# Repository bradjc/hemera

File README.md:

Hemera Indoor Sensor Node
=========================

Hemera is an indoor wireless sensor node that measures temperature, humidity, light and motion.

The node contains three key sensors:
- Sensirion SHT11 (Temperature and Humidity)
- Rohm BH1721 (Light)
- PIR (Motion)

[

](http://www.bradcampbell.com/wp-content/uploads/2012/05/hemera_project.jpg)

Setup
-----

### 1) Clone &amp; install the Lab11 version of tinyos-main:

    git clone https://github.com/lab11/tinyos-main.git
    cd tinyos-main/tools
    ./Bootstrap
    ./configure
    make
    sudo make install

### 2) Clone yours truly:

    git clone https://github.com/lab11/hemera.git

### 3) Add to `bash.rc`:

    export TINYOS_ROOT_DIR=<path to>/tinyos-main
    export TINYOS_ROOT_DIR_ADDITIONAL=<path to>/hemera/tinyos:$TINYOS_ROOT_DIR_ADDITIONAL

### 4) Set up the RaspberryPi (optional, but recommended):

A modified RaspberryPi can be utilized to receive and forward data to GATD. 
If you choose to use one, you need the [Linux CC2520 Driver](https://github.com/ab500/linux-cc2520-driver) for the RPi.
Instead of installing this manually, it is suggested to download &amp; install the preinstalled image from [this torrent](https://github.com/lab11/raspberrypi-cc2520/tree/master/torrents).
Go to https://github.com/lab11/raspberrypi-cc2520 for additional details on setup.

Clone the RPi repo:

    git clone https://github.com/lab11/raspberrypi-cc2520.git

Add to `bash.rc`:

    export TINYOS_ROOT_DIR_ADDITIONAL=<path to>/raspberrypi-cc2520/tinyos:$TINYOS_ROOT_DIR_ADDITIONAL

### 5) Get the compilers

In order to compile the TinyOS code you need the msp430 and the ARM compilers

Sense Stuff
-----------

After you have finsihed the above setup, you should be ready to install apps on the Hemera board.

The basic sense &amp; broadcast app is HemeraAM. To install it, go to `<path to>/hemera/tinyos/apps/HemeraAM` and follow the README. 

To receive &amp; forward data to GATD on the RPi, go to `<path to>/hemera/tinyos/apps/RpiGatdForwarder` and follow the README.

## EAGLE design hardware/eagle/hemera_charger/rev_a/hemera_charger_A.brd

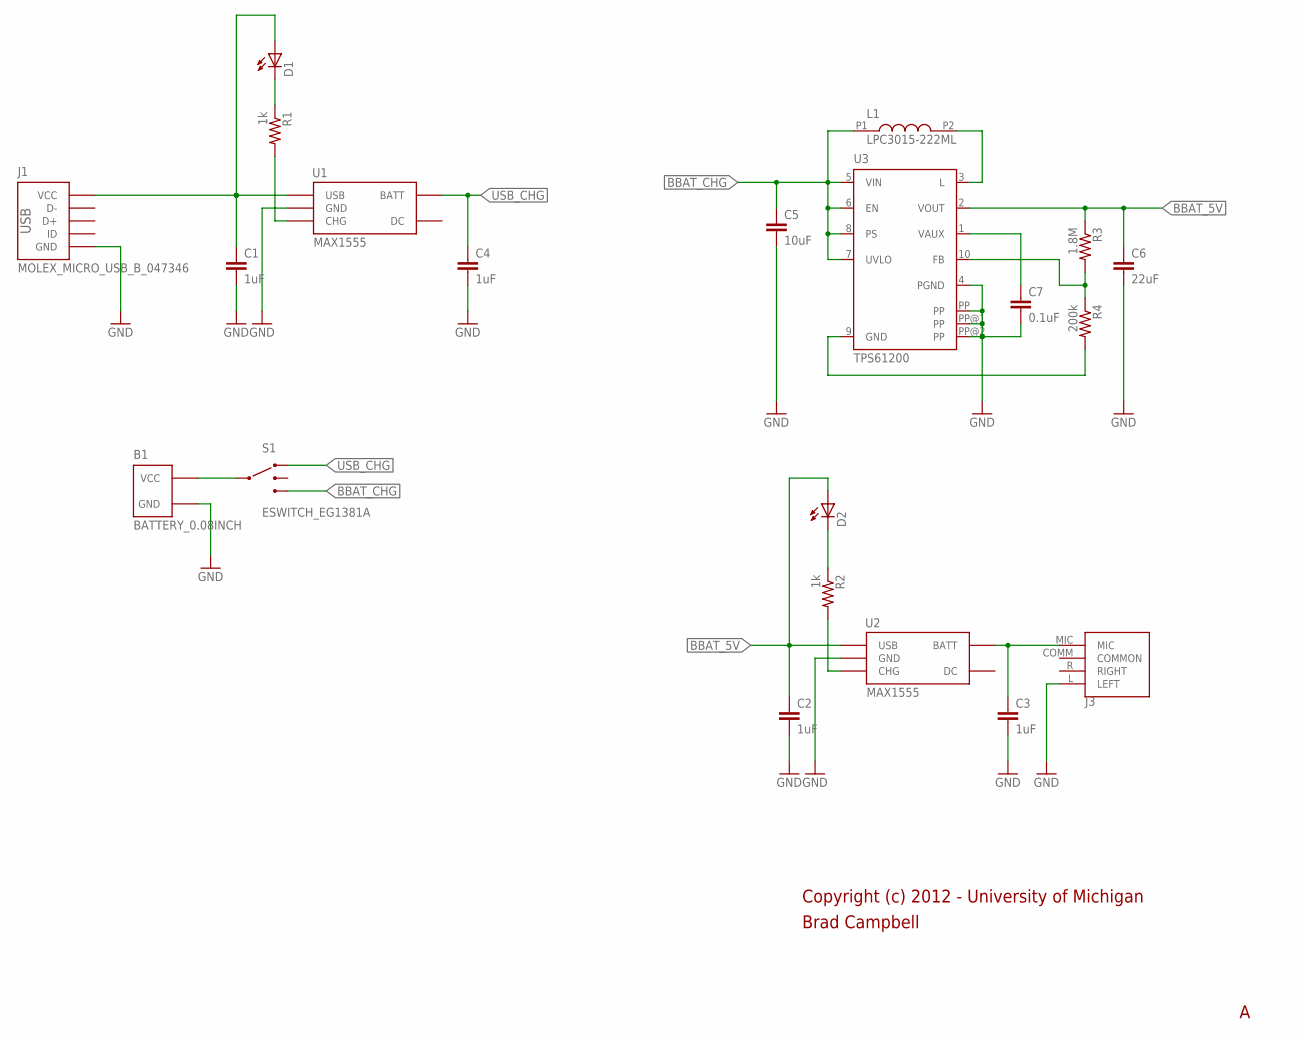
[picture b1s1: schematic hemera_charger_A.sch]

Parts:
B1: BATTERY_0.08INCH
C1, C2, C3, C4: 1uF; C0603
C5: 10uF; C0603
C6: 22uF; C0603
C7: 0.1uF; C0603
D1, D2: LED0603; LED-0603
J1: MOLEX_MICRO_USB_B_047346
J3: 3.5JACK4CONNSUNSTONE_QUICKTURN; PLUGBOARDCONNECTOR_SUNSTONE
L1: LPC3015-222ML; LPS3015
R1, R2: 1k; R0603
R3: 1.8M; R0603
R4: 200k; R0603
S1: ESWITCH_EG1381A; ESWITCH_EG1381
U1, U2: MAX1555; SOT23-5
U3: TPS61200; S-PDSO-N10

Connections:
BBAT: B1.POS (VCC), S1.3
BBAT_5V: C2.1, C6.1, D2.A, R3.1, U2.1 (USB), U3.2 (VOUT)
BBAT_CHG: C5.1, L1.P1 (1), S1.4, U3.5 (VIN), U3.6 (EN), U3.7 (UVLO), U3.8 (PS)
COMMON: J3.COMM (COMMON)
FB: R3.2, R4.1, U3.10 (FB)
GND: B1.NEG (GND), C1.2, C2.2, C3.2, C4.2, C5.2, C6.2, C7.2, J1.GND, J3.L (LEFT), U1.2 (GND), U2.2 (GND), U3.4 (PGND), U3.PP, U3.PP@1 (PP), U3.PP@2 (PP)
L: L1.P2 (2), U3.3 (L)
unnamed: C1.1, D1.A, J1.VCC, U1.1 (USB)
unnamed: R2.2, U2.3 (CHG)
unnamed: C3.1, J3.MIC, U2.5 (BATT)
unnamed: R1.2, U1.3 (CHG)
unnamed: D1.C, R1.1
unnamed: R4.2, U3.9 (GND)
unnamed: D2.C, R2.1
USB_CHG: C4.1, S1.1, U1.5 (BATT)
VAUX: C7.1, U3.1 (VAUX)

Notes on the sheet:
Brad Campbell
Copyright (c) 2012 - University of Michigan

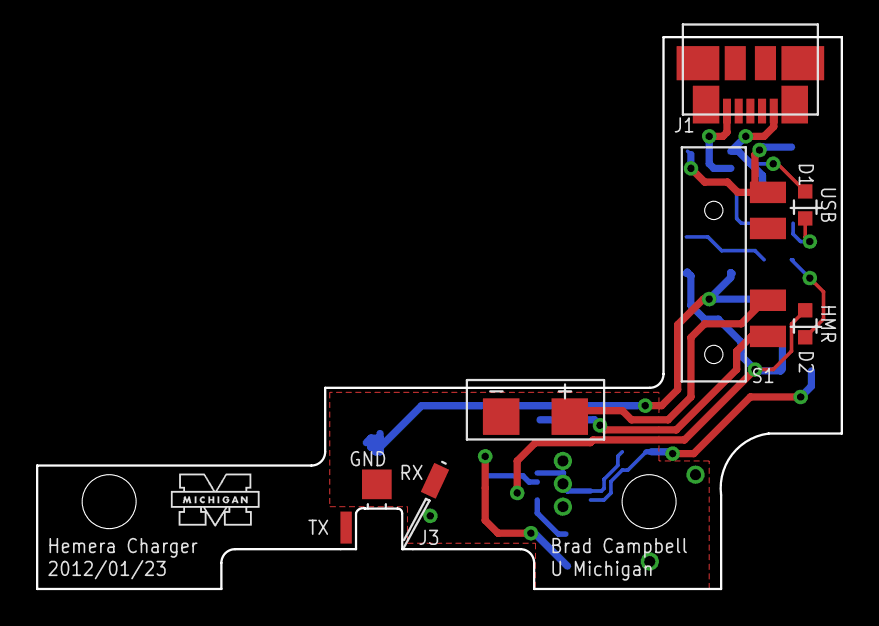
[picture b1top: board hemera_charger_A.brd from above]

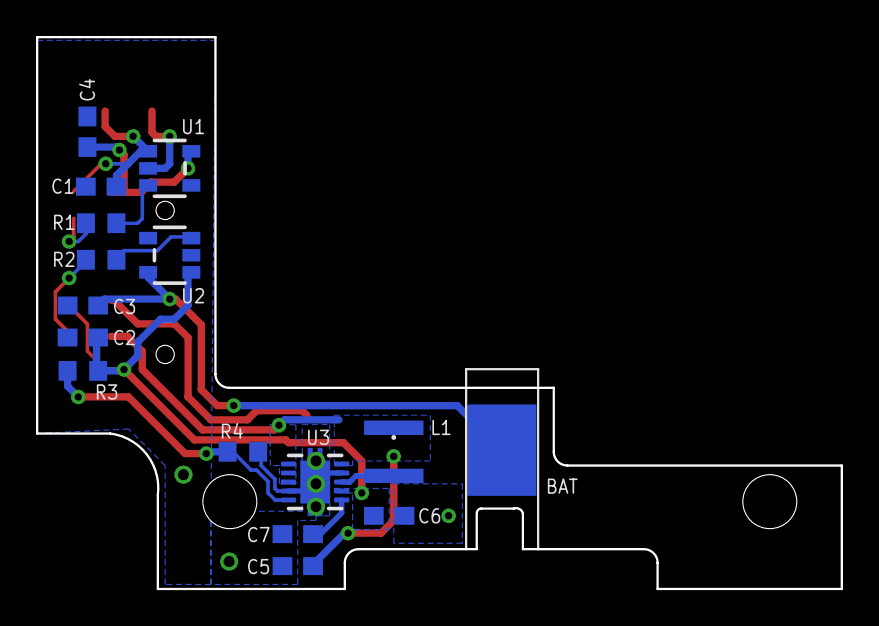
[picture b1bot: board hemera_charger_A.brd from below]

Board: 2 copper layers, 44.7 x 30.7 mm, 22 parts (15 on the bottom side), 15 nets.

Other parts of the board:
U$1: UMICH

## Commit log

2012-01-31 added tinyos folder code
2012-02-01 more gecko tinyos code
2012-02-01 fix to gecko target
2012-02-08 Added a slightly optimized ds2411 driver to the epic chips folder.
    Added new Gecko apps.
2012-02-08 Moved gecko specific chips to their proper locations.
2012-02-09 improving the gecko platform in tinyos
2012-02-09 More moving gecko modules around.
2012-02-09 Added file so the gecko light meter should work with the epic testbed mote again.
    svn is annoying.
2012-02-09 More build
2012-02-09 tinyosifying the gecko rtc
2012-02-14 more gecko code for acks: created module that does data acks in theory at a lower level and is more cc2420 driver like
2012-02-15 whoops forgot a file for the gecko rtc
2012-02-27 re-added powercube.target file
2012-02-27 make powercube install works again
2012-03-03 changes to powercube platform, started debugging radio
2012-03-22 duty cycle manager works maybe
2012-03-22 Cleaned a few things up in the duty cycle manager
2012-07-20 git --> svn cutover
    tinyos/ directory
    commit b016f5c21107cf1e7bf9075cbe033bbac79dc09a
    Author: Pat Pannuto <ppannuto@nuclear.eecs.umich.edu>
    Date: Thu Jul 19 22:13:03 2012 -0400
    Remove extraneous .svn directories
    commit 11ccae6df32e82de854ddd289b2060912456ebe7
2012-09-19 working on android version
2012-10-30 starting on raspberry pi platform
2012-10-30 getting closer to compilation
2012-10-31 more stuff
2012-11-01 raspberry pi platfrom is a little closer to compiling
2012-11-02 gpio for rpi added
2012-11-03 blink MAY actaully work on rpi
2012-11-03 started getting 2520 to compile on epic
2012-11-03 Obey library link order for efficient (by old def) linkers
2012-11-03 Added signalWrapper
2012-11-26 tinyos-ifying the nest code
2012-11-26 added set done to thermostat pins setting this should allow multiple button presses to work
2012-11-28 added hemera project to shed
2012-11-28 oops forgot two hemera files
2012-11-30 temp board tweaks
    fixed hemera makefile
    added figures file to jackit
2012-12-19 compiles with code for talking to the lcd sniffer
2013-01-10 adding better msp interrupt function
2013-01-10 cleaning up door rfid code
2013-01-14 ignores and a first pass on the tinyos cc2520rpi driver
    I've gotten the cc2520rpi driver to compile...but that's about it. I'm not sure all of the files I created will make it into the final version as I'm not quite sure what is handled in tinyos and what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
    Oh, and FUCK SVN.
2013-01-14 removing pi-router stuff that moved to github
2013-01-23 opo.target for opo platform
2013-02-08 removing thermostat stuff from shed
2013-02-22 Adding coilcube platform for sdebruin
2013-02-23 modified coilcube target file to accurately reflect folder names
2013-03-08 make coilcube
2013-03-08 coilcube target
2013-03-08 fkdjsla
2013-03-09 thin radio driver for coilcube now compiles
2013-03-09 getting closer to having bare cc2420fb driver working with coilcube
2013-03-10 crispy thin fast boot 2420 driver can now send packets
2013-03-25 Start to explaining how to use this device.
2013-03-25 re-wrote bh17 light sensor driver to make more sense now that I know how to write tinyos drivers better
2013-03-25 and the p file
2013-03-25 removing old files from the driver
2013-03-25 nice hpl file for light sensor on hemera
2013-03-25 cleaned up .platform file
2013-03-25 removing old interface and fixed comments on driver
2013-03-25 fixed comment
2013-03-25 added new lightsensor directories
2013-03-25 cleaned up the hemera sampler app. Made it easier to read and extend
2013-03-25 small edits to rohm test app
2013-03-25 imported the hemera platform files
2013-03-25 moved files to the correct location
2013-03-25 not relevant
2013-03-25 correct spot
2013-03-25 correct folder tree
2013-03-25 moved to correct directory
2013-03-25 moved to correct dir
2013-03-25 moved .platform file
2013-03-25 removed old include directories
2013-03-25 added build directories to gitignore
2013-09-13 ignore hardware
2013-09-13 better git ignore
2013-09-13 accidentally reverted my changes
2013-12-31 added pcb docs
2013-12-31 add hemera a docs
2014-03-04 updated hemera to new make system
2014-03-04 updated makefile to new blip style
2014-03-04 updated to UM mac addr
2014-03-04 added new "monjolo" style app
    just sends a broadcast packet each minute
2014-03-04 added gitignore
2014-03-04 added info file
2014-03-05 updated hemeramonjolo app
    now sends profile_id so gatd knows what to do
2014-06-13 Enable user button functionality
2014-06-19 Add HemeraAM app to repo
2014-06-30 Add RpiGatdForwarder app
2014-07-03 Added pre-compiled RpiGatdForwarderC app
2014-07-03 Add HemeraBlip app
2014-07-03 Add Hemstera, Hemera motion-based hue light control
2014-07-03 Fix HemeraBlip README
2014-07-03 Add tessel implementation of Hemera
2014-07-11 Add README for Tessel implementation, which is also now streaming to GATD
2014-08-01 fixed byte indexes
2014-08-01 readme tinyos branch updated
